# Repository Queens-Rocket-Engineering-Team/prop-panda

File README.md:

# PANDA Control Board

PANDA (Propulsion Actuation and Nominal Data Acquisition) is the control PCB for the Queen's Rocket Engineering Team's
hybrid rocket engine. During launch, PANDA controls systems on the fill plumbing panel, controls rocket ignition, and
provides pre-launch data acquisition. PANDA also functions as a standalone static fire test stand controller that
can execute all aspects of a hot-fire test.

## Assembled PCB

## System Architecture

PANDA uses an ESP32S3-WROOM-1U microcontroller for systems control. This ESP32S3 communicates with an external control
server to for remote control and data streaming over 2.4GHz WiFi. All commands are sent from the external server, as
PANDA does not autonomously control any systems.

Five ADS112C04 ADCs provide sensor readings to the ESP32S3 over an I2C bus. Sensors supported are:

- 6 pressure transducers
- 4 thermocouples
- 2 load cells

PANDA is also capable of monitoring ignitor characteristics. Measurements of the current passing through a nichrome wire
ignitor are obtained using a current sense amplifier across a shunt resistor in the ignitor path. Ignitor resistance
readings are also measured by injecting a small current from an IDAC on an ADC, and
measuring the resulting voltage.

A communications diagram for PANDA can be seen below.

```mermaid
---
title: PANDA Communications Flow
---
flowchart LR

    ADC(ADS112C04<br>ADCs) <==I2C==> ESP(ESP32 MCU)

    subgraph Controls
        AV(Actuated Valves)
        24VSAFE[24VSAFE<br>Relay]
        RUN[Ignitor Run<br>Relay]
        PRIME[Ignitor Prime<br>Relay]
    end

    subgraph Sensors
        PT(Pressure Transducers)
        TC(Thermocouples)
        LC(Load Cells)
        CUR(Ignitor Current)
        RES(Ignitor Resistance)
    end

    PT --> ADC
    TC --> ADC
    LC --> ADC
    CUR --> ADC
    RES --> ADC

    ESP --> AV
    ESP -->24VSAFE
    ESP --> RUN
    ESP --> PRIME

    ESP <-. WiFI .-> WIFI(External Server)
```

## Power Architecture

PANDA operates from a 24VDC power supply, and has a maximum current rating of 10A. The 24V rail is first stepped down to 5.3V with a switching converter and then dropped to 5V and 3.3V with LDOs. The 5V rail supplies analog systems, and the 3.3V rail supplies digital systems. Using LDOs on the switching output allows for low-noise power for analog measurements.

The 24VSAFE rail is only be energized when the fill panel is vacated, as it powers hazardous components such as the ignitor. The ignitor utilizes two relays in series for additional redundancy, and to ensure ignition is always intentional. A power distribution chart of PANDA can be seen below. This graph does not include the power sequencing and filtering present on the board.

```mermaid
---
title: PANDA Power Distribution
---
flowchart LR

    24VIN([24VIN]) --> 24VSAFE[24VSAFE<br>Relay]

    subgraph Valves
        AV(Valves)
        AVSAFE(Fill Valve<br>Run Valve)
    end
    24VIN --> AV
    24VSAFE --> AVSAFE

    subgraph Ignitor
        RUN[Ignitor Run<br>Relay]
        RUN --> PRIME[Ignitor Prime<br>Relay]
        PRIME --> IGN(Ignitor)
    end

    24VSAFE --> RUN[Ignitor Run<br>Relay]

    subgraph Voltage Regulation
        BUCK([5.3V Buck])
        BUCK --> 5V([5V LDO])
        BUCK --> 3V3([3.3V LDO])
    end

    24VIN --> BUCK([5.3V Buck])

    subgraph Sensors
        PT(Pressure Transducers)
        LC(Load Cells)
        RES(Ignitor Current<br>Sensor)
    end

    5V --> ADC(ADS112C04<br>ADCs)
    3V3 --> ESP(ESP32 MCU)
    3V3 --> ADC
    24VIN --> PT
    5V --> LC
    5V --> RES
```

## Required Software

This project was created using KiCad v9.0. If manufacturing with JLCPCB, install the Fabrication Toolkit KiCad plugin for JLCPCB.

## Recommended Manufacturing Options

If ordering from JLCPCB, use the JLC04161H-3313 stackup option. For JLC PCBA, the standard PCBA option is required due
to the ESP32S3-WROOM-1U being unavailable as a part in the economic PCBA assembly.

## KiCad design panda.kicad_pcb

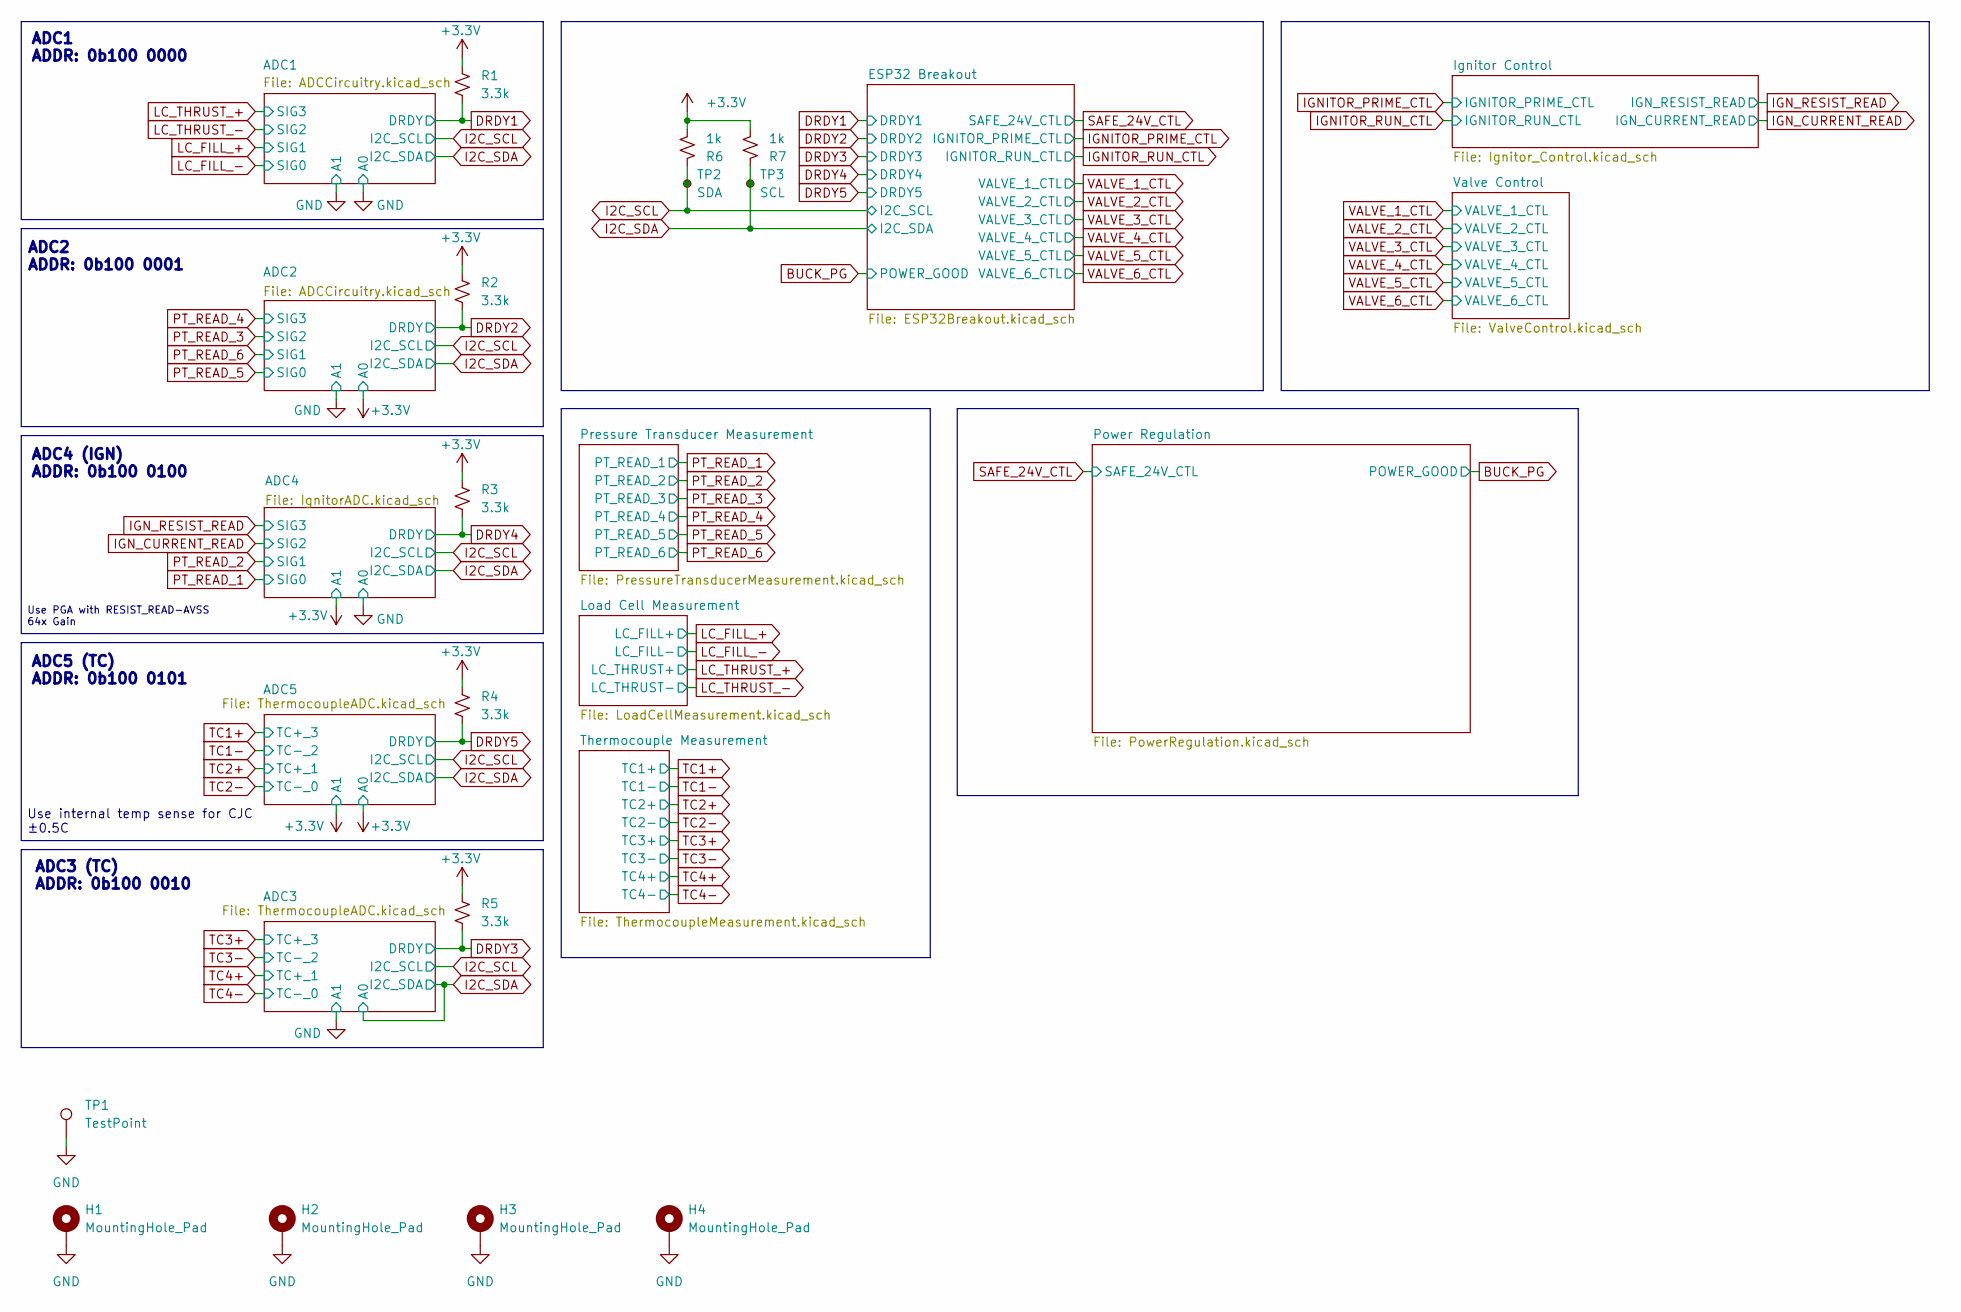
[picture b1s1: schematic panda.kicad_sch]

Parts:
H1, H2, H3, H4: MountingHole_Pad; MountingHole_3.2mm_M3_ISO7380_Pad
R1, R2, R3, R4, R5: 3.3k; R_0402_1005Metric; MPN 0402WGF3301TCE; LCSC C25890
R6, R7: 1k; R_0402_1005Metric; LCSC C11702
TP1: TestPoint; TestPoint_Loop_D2.50mm_Drill1.0mm
TP2: SDA; TestPoint_Pad_D1.5mm
TP3: SCL; TestPoint_Pad_D1.5mm

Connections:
DRDY1: R1.2; also elsewhere on the board
DRDY2: R2.2; also elsewhere on the board
DRDY3: R5.2; also elsewhere on the board
DRDY4: R3.2; also elsewhere on the board
DRDY5: R4.2; also elsewhere on the board
I2C_SCL: R6.1, TP2.1; also elsewhere on the board
I2C_SDA: R7.1, TP3.1; also elsewhere on the board

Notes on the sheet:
ADC2 ADDR: 0b100 0001
ADC4 (IGN) ADDR: 0b100 0100
Use PGA with RESIST_READ-AVSS 64x Gain
ADC1 ADDR: 0b100 0000
ADC3 (TC) ADDR: 0b100 0010
Use internal temp sense for CJC ±0.5C
ADC5 (TC) ADDR: 0b100 0101

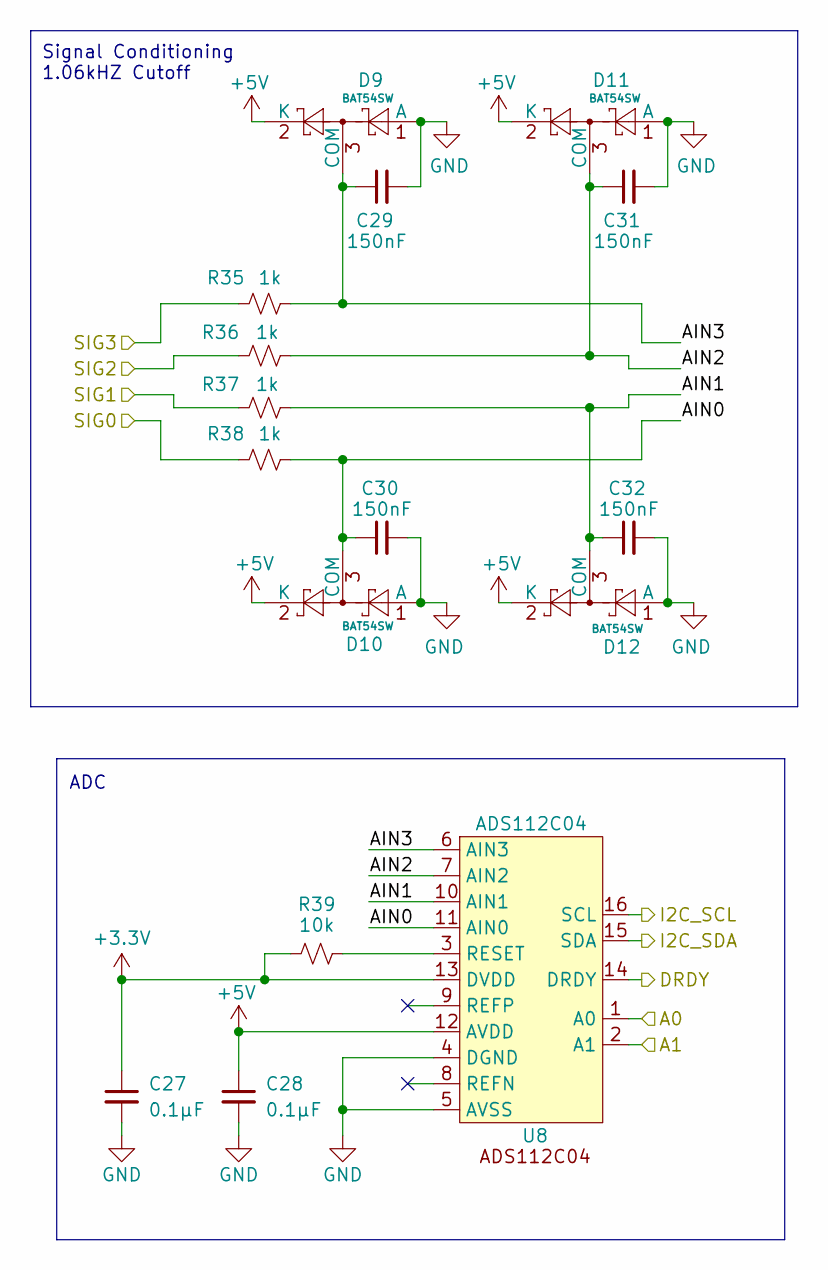
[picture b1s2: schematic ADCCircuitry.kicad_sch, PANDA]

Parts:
C27, C28: 0.1μF; C_0402_1005Metric; MPN CL05B104KO5NNNC; LCSC C307331
C29, C30, C31, C32: 150nF; C_0402_1005Metric; LCSC C576725
D9, D10, D11, D12: BAT54SW; SOT-323_SC-70; LCSC C83575
R35, R36, R37, R38: 1k; R_0402_1005Metric
R39: 10k; R_0402_1005Metric; MPN 0402WGJ0103TCE; LCSC C25531
U8: ADS112C04; TSSOP-16_4.4x5mm_P0.65mm; MPN ADS112C04IPWR; LCSC C701615

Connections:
+5V: C28.1, D9.2 (K), D10.2 (K), D11.2 (K), D12.2 (K), U8.12 (AVDD); also elsewhere on the board
/ADC1/AIN0: C30.1, D10.3 (COM), R38.2, U8.11 (AIN0)
/ADC1/AIN1: C32.1, D12.3 (COM), R37.2, U8.10 (AIN1)
/ADC1/AIN2: C31.1, D11.3 (COM), R36.2, U8.7 (AIN2)
/ADC1/AIN3: C29.1, D9.3 (COM), R35.2, U8.6 (AIN3)
DRDY1: U8.14 (DRDY); also elsewhere on the board
I2C_SCL: U8.16 (SCL); also elsewhere on the board
I2C_SDA: U8.15 (SDA); also elsewhere on the board
LC_FILL_+: R37.1; also elsewhere on the board
LC_FILL_-: R38.1; also elsewhere on the board
LC_THRUST_+: R35.1; also elsewhere on the board
LC_THRUST_-: R36.1; also elsewhere on the board
unnamed: R39.2, U8.3 (RESET)

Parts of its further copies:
C33, C34: 0.1μF; C_0402_1005Metric; MPN CL05B104KO5NNNC; LCSC C307331
C35, C36, C37, C38: 150nF; C_0402_1005Metric; LCSC C576725
D13, D14, D15, D16: BAT54SW; SOT-323_SC-70; LCSC C83575
R40, R41, R42, R43: 1k; R_0402_1005Metric
R44: 10k; R_0402_1005Metric; MPN 0402WGJ0103TCE; LCSC C25531
U9: ADS112C04; TSSOP-16_4.4x5mm_P0.65mm; MPN ADS112C04IPWR; LCSC C701615

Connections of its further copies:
+5V: C34.1, D13.2 (K), D14.2 (K), D15.2 (K), D16.2 (K), U9.12 (AVDD); also elsewhere on the board
/ADC2/AIN0: C36.1, D14.3 (COM), R43.2, U9.11 (AIN0)
/ADC2/AIN1: C38.1, D16.3 (COM), R42.2, U9.10 (AIN1)
/ADC2/AIN2: C37.1, D15.3 (COM), R41.2, U9.7 (AIN2)
/ADC2/AIN3: C35.1, D13.3 (COM), R40.2, U9.6 (AIN3)
DRDY2: U9.14 (DRDY); also elsewhere on the board
I2C_SCL: U9.16 (SCL); also elsewhere on the board
I2C_SDA: U9.15 (SDA); also elsewhere on the board
unnamed: R44.2, U9.3 (RESET)
PT_READ_3: R41.1; also elsewhere on the board
PT_READ_4: R40.1; also elsewhere on the board
PT_READ_5: R43.1; also elsewhere on the board
PT_READ_6: R42.1; also elsewhere on the board

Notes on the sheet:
ADC
Signal Conditioning 1.06kHZ Cutoff

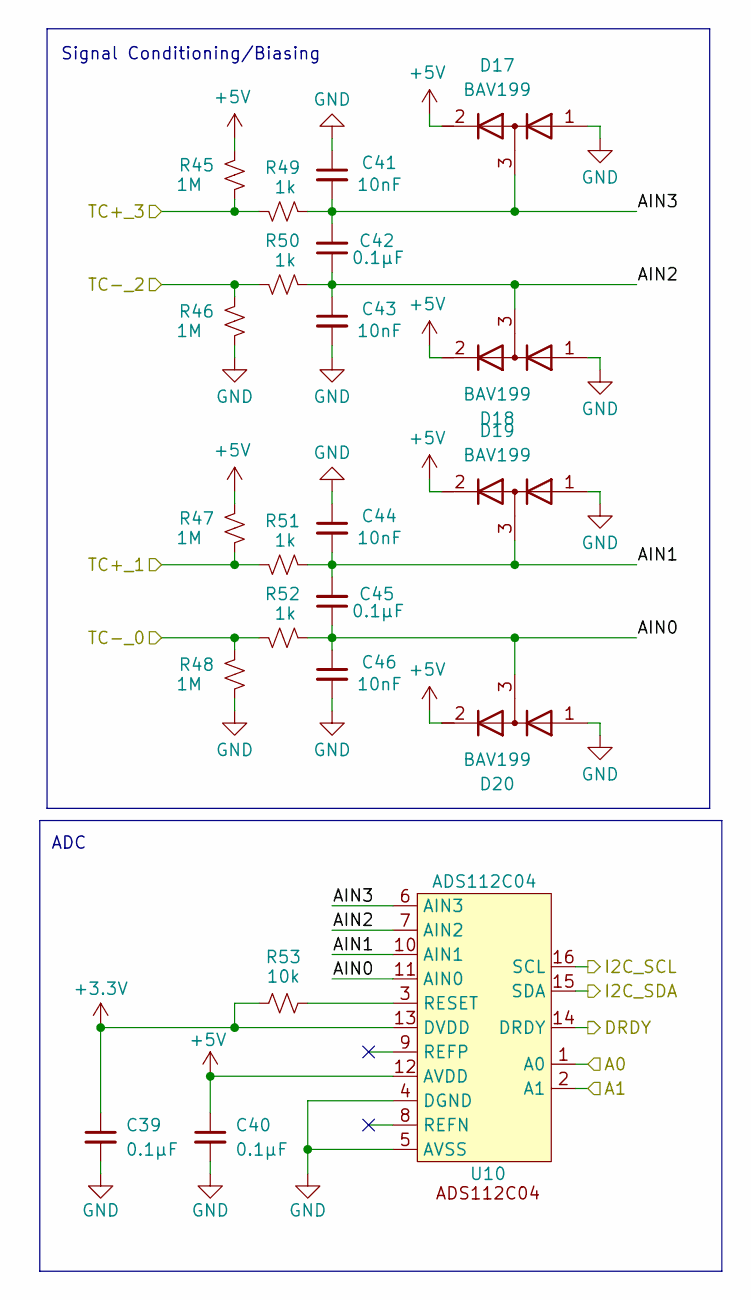
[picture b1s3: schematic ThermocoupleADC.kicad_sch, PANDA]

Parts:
C39, C40, C42, C45: 0.1μF; C_0402_1005Metric; MPN CL05B104KO5NNNC; LCSC C307331
C41, C43, C44, C46: 10nF; C_0603_1608Metric; LCSC C5299898
D17, D18, D19, D20: BAV199; SOT-23; LCSC C40919
R45, R46, R47, R48: 1M; R_0402_1005Metric
R49, R50, R51, R52: 1k; R_0402_1005Metric
R53: 10k; R_0402_1005Metric; MPN 0402WGJ0103TCE; LCSC C25531
U10: ADS112C04; TSSOP-16_4.4x5mm_P0.65mm; MPN ADS112C04IPWR; LCSC C701615

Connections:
+5V: C40.1, D17.2 (K), D18.2 (K), D19.2 (K), D20.2 (K), R45.2, R47.2, U10.12 (AVDD); also elsewhere on the board
/ADC5/AIN0: C45.1, C46.1, D20.3 (common), R52.2, U10.11 (AIN0)
/ADC5/AIN1: C44.2, C45.2, D19.3 (common), R51.2, U10.10 (AIN1)
/ADC5/AIN2: C42.1, C43.1, D18.3 (common), R50.2, U10.7 (AIN2)
/ADC5/AIN3: C41.2, C42.2, D17.3 (common), R49.2, U10.6 (AIN3)
DRDY5: U10.14 (DRDY); also elsewhere on the board
I2C_SCL: U10.16 (SCL); also elsewhere on the board
I2C_SDA: U10.15 (SDA); also elsewhere on the board
unnamed: R53.2, U10.3 (RESET)
TC1+: R45.1, R49.1; also elsewhere on the board
TC1-: R46.2, R50.1; also elsewhere on the board
TC2+: R47.1, R51.1; also elsewhere on the board
TC2-: R48.2, R52.1; also elsewhere on the board

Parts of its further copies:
C47, C48, C50, C53: 0.1μF; C_0402_1005Metric; MPN CL05B104KO5NNNC; LCSC C307331
C49, C51, C52, C54: 10nF; C_0603_1608Metric; LCSC C5299898
D21, D22, D23, D24: BAV199; SOT-23; LCSC C40919
R54, R55, R56, R57: 1M; R_0402_1005Metric
R58, R59, R60, R61: 1k; R_0402_1005Metric
R62: 10k; R_0402_1005Metric; MPN 0402WGJ0103TCE; LCSC C25531
U11: ADS112C04; TSSOP-16_4.4x5mm_P0.65mm; MPN ADS112C04IPWR; LCSC C701615

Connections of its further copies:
+5V: C48.1, D21.2 (K), D22.2 (K), D23.2 (K), D24.2 (K), R54.2, R56.2, U11.12 (AVDD); also elsewhere on the board
/ADC3/AIN0: C53.1, C54.1, D24.3 (common), R61.2, U11.11 (AIN0)
/ADC3/AIN1: C52.2, C53.2, D23.3 (common), R60.2, U11.10 (AIN1)
/ADC3/AIN2: C50.1, C51.1, D22.3 (common), R59.2, U11.7 (AIN2)
/ADC3/AIN3: C49.2, C50.2, D21.3 (common), R58.2, U11.6 (AIN3)
DRDY3: U11.14 (DRDY); also elsewhere on the board
I2C_SCL: U11.16 (SCL); also elsewhere on the board
I2C_SDA: U11.1 (A0), U11.15 (SDA); also elsewhere on the board
unnamed: R62.2, U11.3 (RESET)
TC3+: R54.1, R58.1; also elsewhere on the board
TC3-: R55.2, R59.1; also elsewhere on the board
TC4+: R56.1, R60.1; also elsewhere on the board
TC4-: R57.2, R61.1; also elsewhere on the board

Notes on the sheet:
ADC
Signal Conditioning/Biasing

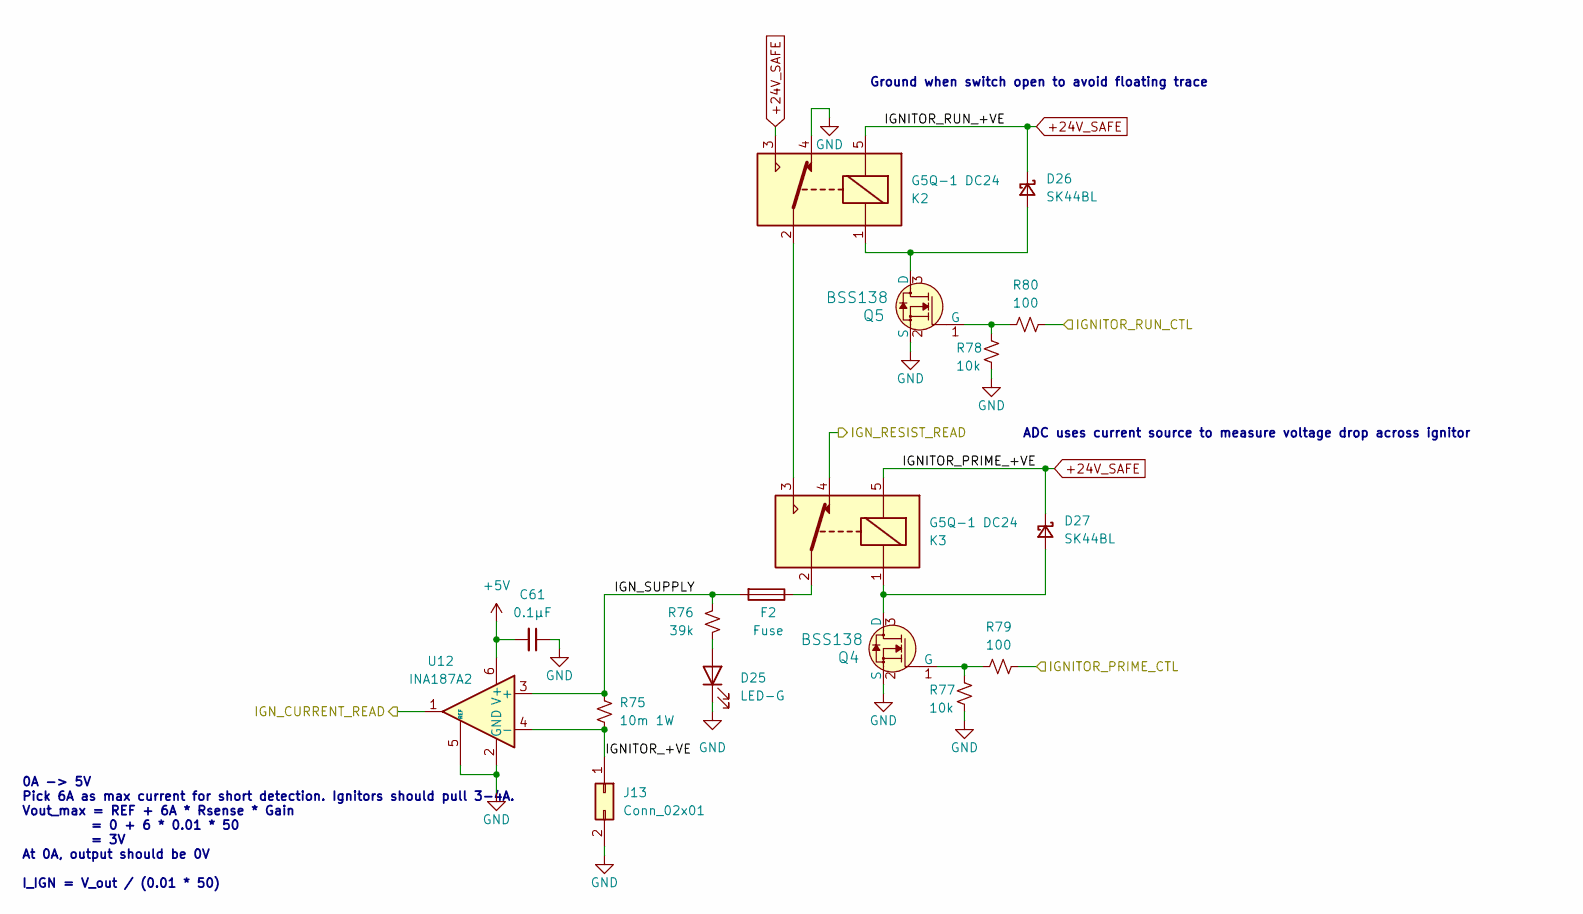
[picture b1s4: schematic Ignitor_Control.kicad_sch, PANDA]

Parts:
C61: 0.1μF; C_0402_1005Metric; MPN CL05B104KO5NNNC; LCSC C307331
D25: LED-G; LED_0805_2012Metric; LCSC C2297
D26, D27: SK44BL; D_SMB; MPN SK44BL-TP; LCSC C151740
F2: Fuse; Fuseholder_Blade_Mini_Keystone_3568
J13: Conn_02x01; Molex_Mini-Fit_Jr_5566-02A_2x01_P4.20mm_Vertical
K2, K3: G5Q-1 DC24; Relay_SPDT_Omron-G5Q-1
Q4, Q5: BSS138; SOT-23-3; MPN BSS138; LCSC C8490
R75: 10m 1W; R_1206_3216Metric
R76: 39k; R_0402_1005Metric
R77, R78: 10k; R_0402_1005Metric; MPN 0402WGJ0103TCE; LCSC C25531
R79, R80: 100; R_0402_1005Metric; MPN 0402WGF1000TCE; LCSC C25076
U12: INA187A2; SOT-23-6; LCSC C49262295

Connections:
+5V: C61.2, U12.6 (V+); also elsewhere on the board
+24V_SAFE: D26.1 (K), D27.1 (K), K2.3, K2.5, K3.5; also elsewhere on the board
/Ignitor Control/IGNITOR_+VE: J13.1, R75.2, U12.4 (-)
/Ignitor Control/IGN_SUPPLY: F2.2, R75.1, R76.2, U12.3 (+)
IGNITOR_PRIME_CTL: R79.2; also elsewhere on the board
IGNITOR_RUN_CTL: R80.2; also elsewhere on the board
IGN_CURRENT_READ: U12.1; also elsewhere on the board
IGN_RESIST_READ: K3.4; also elsewhere on the board
unnamed: D25.2 (A), R76.1
unnamed: D26.2 (A), K2.1, Q5.3 (D)
unnamed: D27.2 (A), K3.1, Q4.3 (D)
unnamed: F2.1, K3.2
unnamed: K2.2, K3.3
unnamed: Q4.1 (G), R77.1, R79.1
unnamed: Q5.1 (G), R78.1, R80.1

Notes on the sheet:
0A -> 5V Pick 6A as max current for short detection. Ignitors should pull 3-4A. Vout_max = REF + 6A * Rsense * Gain = 0 + 6 * 0.01 * 50 = 3V At 0A, output should be 0V I_IGN = V_out / (0.01 * 50)
Ground when switch open to avoid floating trace
ADC uses current source to measure voltage drop across ignitor

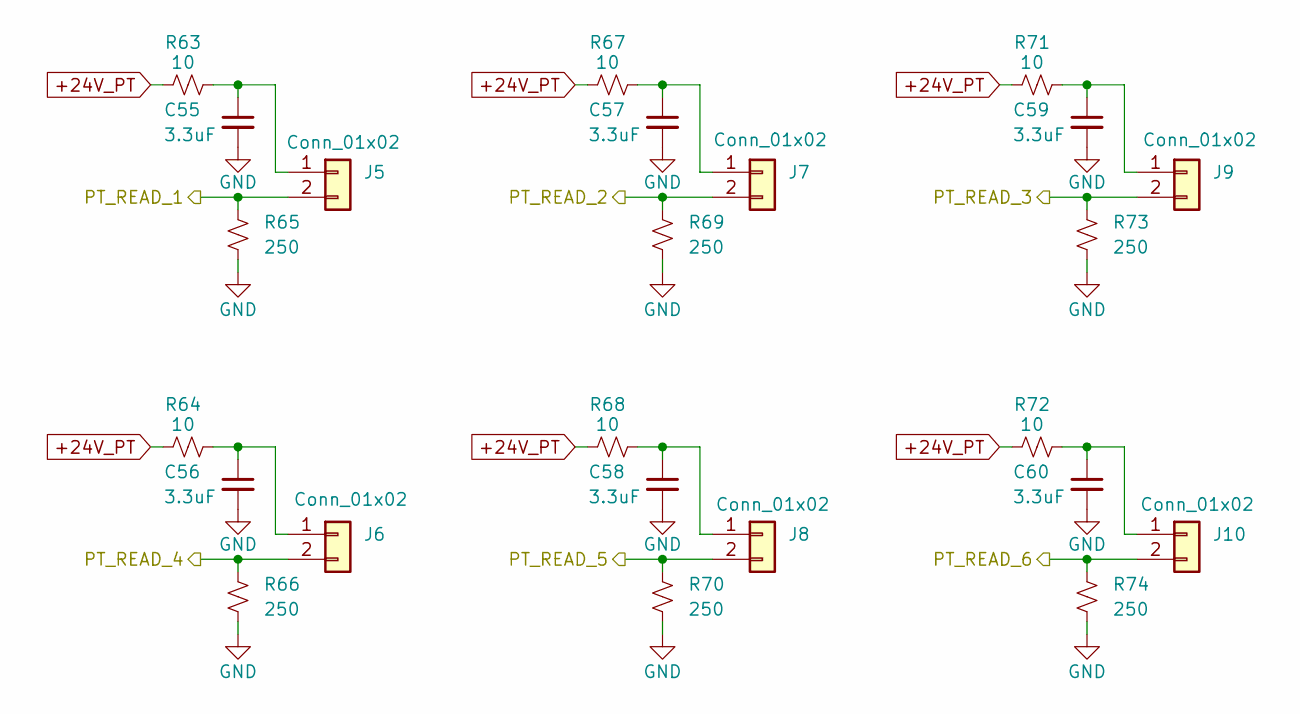
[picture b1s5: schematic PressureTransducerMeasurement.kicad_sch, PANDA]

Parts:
C55, C56, C57, C58, C59, C60: 3.3uF; C_0805_2012Metric; LCSC C342775
J5, J6, J7, J8, J9, J10: Conn_01x02; Molex_Micro-Fit_3.0_43650-0215_1x02_P3.00mm_Vertical
R63, R64, R67, R68, R71, R72: 10; R_0402_1005Metric
R65, R66, R69, R70, R73, R74: 250; R_0603_1608Metric; MPN RT0603BRE07250RL; LCSC C861779

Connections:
+24V_PT: R63.1, R64.1, R67.1, R68.1, R71.1, R72.1; also elsewhere on the board
unnamed: C55.1, J5.1, R63.2
unnamed: C56.1, J6.1, R64.2
unnamed: C57.1, J7.1, R67.2
unnamed: C58.1, J8.1, R68.2
unnamed: C59.1, J9.1, R71.2
unnamed: C60.1, J10.1, R72.2
PT_READ_1: J5.2, R65.1; also elsewhere on the board
PT_READ_2: J7.2, R69.1; also elsewhere on the board
PT_READ_3: J9.2, R73.1; also elsewhere on the board
PT_READ_4: J6.2, R66.1; also elsewhere on the board
PT_READ_5: J8.2, R70.1; also elsewhere on the board
PT_READ_6: J10.2, R74.1; also elsewhere on the board

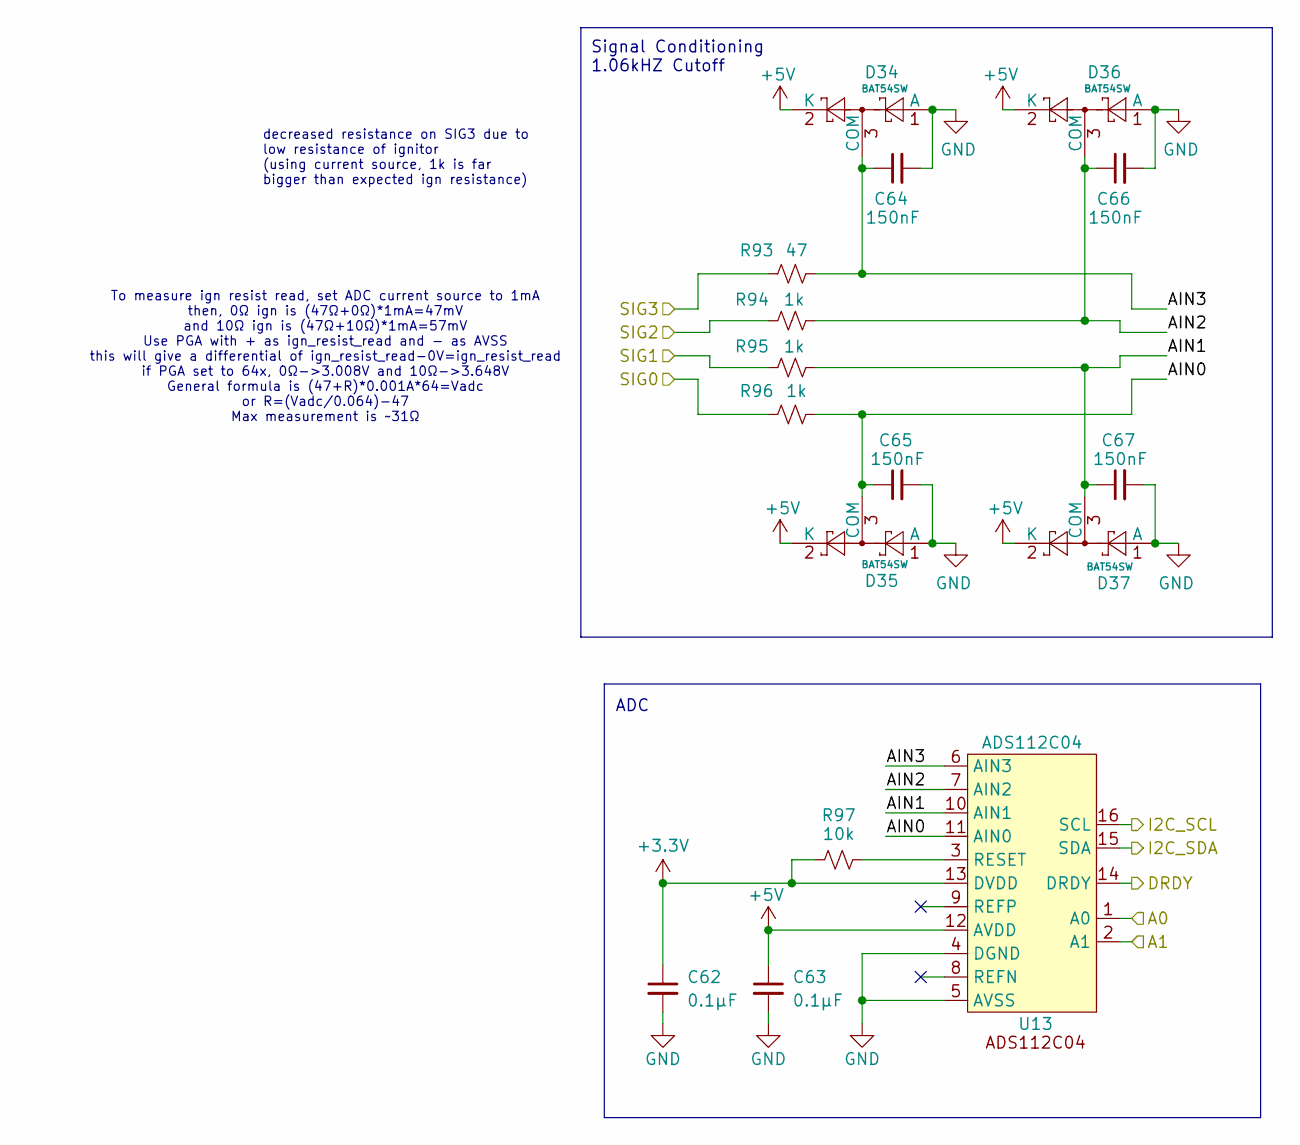
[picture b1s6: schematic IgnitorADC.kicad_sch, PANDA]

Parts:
C62, C63: 0.1μF; C_0402_1005Metric; MPN CL05B104KO5NNNC; LCSC C307331
C64, C65, C66, C67: 150nF; C_0402_1005Metric; LCSC C576725
D34, D35, D36, D37: BAT54SW; SOT-323_SC-70; LCSC C83575
R93: 47; R_0402_1005Metric; LCSC C445569
R94, R95, R96: 1k; R_0402_1005Metric
R97: 10k; R_0402_1005Metric; MPN 0402WGJ0103TCE; LCSC C25531
U13: ADS112C04; TSSOP-16_4.4x5mm_P0.65mm; MPN ADS112C04IPWR; LCSC C701615

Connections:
+5V: C63.1, D34.2 (K), D35.2 (K), D36.2 (K), D37.2 (K), U13.12 (AVDD); also elsewhere on the board
/ADC4/AIN0: C65.1, D35.3 (COM), R96.2, U13.11 (AIN0)
/ADC4/AIN1: C67.1, D37.3 (COM), R95.2, U13.10 (AIN1)
/ADC4/AIN2: C66.1, D36.3 (COM), R94.2, U13.7 (AIN2)
/ADC4/AIN3: C64.1, D34.3 (COM), R93.2, U13.6 (AIN3)
DRDY4: U13.14 (DRDY); also elsewhere on the board
I2C_SCL: U13.16 (SCL); also elsewhere on the board
I2C_SDA: U13.15 (SDA); also elsewhere on the board
IGN_CURRENT_READ: R94.1; also elsewhere on the board
IGN_RESIST_READ: R93.1; also elsewhere on the board
unnamed: R97.2, U13.3 (RESET)
PT_READ_1: R96.1; also elsewhere on the board
PT_READ_2: R95.1; also elsewhere on the board

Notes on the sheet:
To measure ign resist read, set ADC current source to 1mA then, 0Ω ign is (47Ω+0Ω)*1mA=47mV and 10Ω ign is (47Ω+10Ω)*1mA=57mV Use PGA with + as ign_resist_read and - as AVSS this will give a differential of ign_resist_read-0V=ign_resist_read if PGA set to 64x, 0Ω->3.008V and 10Ω->3.648V General for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
ADC
decreased resistance on SIG3 due to low resistance of ignitor (using current source, 1k is far bigger than expected ign resistance)
Signal Conditioning 1.06kHZ Cutoff

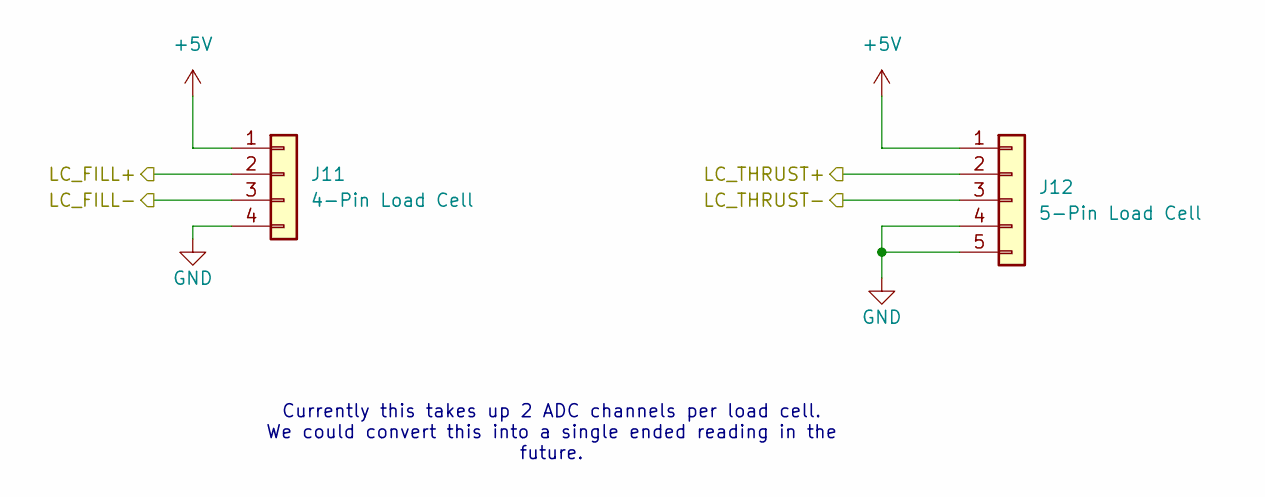
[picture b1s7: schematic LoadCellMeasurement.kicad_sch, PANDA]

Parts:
J11: 4-Pin Load Cell; Molex_Micro-Fit_3.0_43650-0415_1x04_P3.00mm_Vertical
J12: 5-Pin Load Cell; Molex_Micro-Fit_3.0_43650-0515_1x05_P3.00mm_Vertical

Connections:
+5V: J11.1, J12.1; also elsewhere on the board
LC_FILL_+: J11.2; also elsewhere on the board
LC_FILL_-: J11.3; also elsewhere on the board
LC_THRUST_+: J12.2; also elsewhere on the board
LC_THRUST_-: J12.3; also elsewhere on the board

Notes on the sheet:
Currently this takes up 2 ADC channels per load cell. We could convert this into a single ended reading in the future.

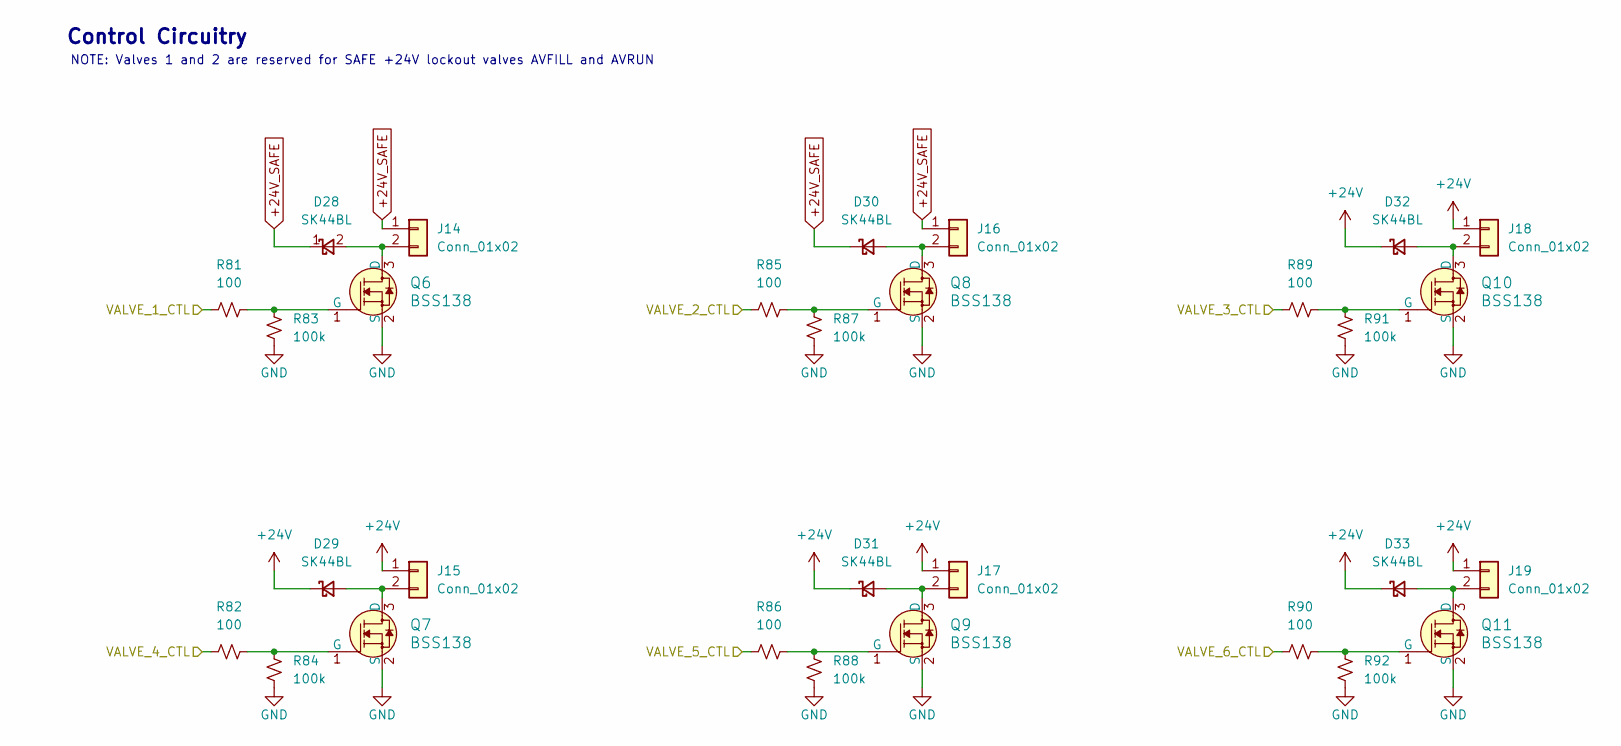
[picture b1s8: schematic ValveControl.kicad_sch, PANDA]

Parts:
D28, D29, D30, D31, D32, D33: SK44BL; D_SMB; MPN SK44BL-TP; LCSC C151740
J14, J15, J16, J17, J18, J19: Conn_01x02; Molex_Micro-Fit_3.0_43650-0215_1x02_P3.00mm_Vertical
Q6, Q7, Q8, Q9: BSS138; SOT-23-3; MPN BSS138; LCSC C8490
Q10, Q11: BSS138; SOT-23-3; MPN BSS138; Digi-Key_PN BSS138CT-ND
R81, R82, R85, R86, R89, R90: 100; R_0402_1005Metric; MPN 0402WGF1000TCE; LCSC C25076
R83, R84, R87, R88, R91, R92: 100k; R_0603_1608Metric; MPN 0402WGJ0104TCE; LCSC C25530

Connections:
+24V: D29.1 (K), D31.1 (K), D32.1 (K), D33.1 (K), J15.1, J17.1, J18.1, J19.1; also elsewhere on the board
+24V_SAFE: D28.1 (K), D30.1 (K), J14.1, J16.1; also elsewhere on the board
unnamed: D28.2 (A), J14.2, Q6.3 (D)
unnamed: D29.2 (A), J15.2, Q7.3 (D)
unnamed: D30.2 (A), J16.2, Q8.3 (D)
unnamed: D31.2 (A), J17.2, Q9.3 (D)
unnamed: D32.2 (A), J18.2, Q10.3 (D)
unnamed: D33.2 (A), J19.2, Q11.3 (D)
unnamed: Q6.1 (G), R81.2, R83.1
unnamed: Q7.1 (G), R82.2, R84.1
unnamed: Q8.1 (G), R85.2, R87.1
unnamed: Q9.1 (G), R86.2, R88.1
unnamed: Q10.1 (G), R89.2, R91.1
unnamed: Q11.1 (G), R90.2, R92.1
VALVE_1_CTL: R81.1; also elsewhere on the board
VALVE_2_CTL: R85.1; also elsewhere on the board
VALVE_3_CTL: R89.1; also elsewhere on the board
VALVE_4_CTL: R82.1; also elsewhere on the board
VALVE_5_CTL: R86.1; also elsewhere on the board
VALVE_6_CTL: R90.1; also elsewhere on the board

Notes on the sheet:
NOTE: Valves 1 and 2 are reserved for SAFE +24V lockout valves AVFILL and AVRUN
Control Circuitry

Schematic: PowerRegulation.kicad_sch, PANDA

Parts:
BZ1: YS-SBZ9650DYB05; LCSC C409830
C1, C7, C14, C15, C18, C19, C21: 0.1μF; C_0402_1005Metric; MPN CL05B104KO5NNNC; LCSC C307331
C2: 100uF; CP_Elec_10x10; LCSC C161937
C3: 10uF; C_1812_4532Metric; Voltage 50V
C4: 10uF; C_1206_3216Metric; Voltage 50V; LCSC C13585
C5: 220nF; C_0805_2012Metric; Voltage 50V; LCSC C5378
C6: 1uF; C_0603_1608Metric; LCSC C29936
C8, C13, C17, C20: 10uF; C_0805_2012Metric; LCSC C15850
C9: 3pF; C_0603_1608Metric; LCSC C695157
C10, C12: 22uF; C_0805_2012Metric; LCSC C602037
C11: 10nF; C_0402_1005Metric; LCSC C15195
C16: 2.2uF; C_0603_1608Metric; LCSC C23630
D1, D3, D4, D6, D7: LED-G; LED_0805_2012Metric; LCSC C2297
D2: SMCJ26A-13-F; D_SMC; LCSC C135156
D5, D38: SK44BL; D_SMB; MPN SK44BL-TP; LCSC C151740
F1: Fuse; Fuseholder_Blade_Mini_Keystone_3568
J1: Conn_01x02; Molex_Micro-Fit_3.0_43650-0215_1x02_P3.00mm_Vertical
J2, J3: Conn_02x01; Molex_Mini-Fit_Jr_5566-02A_2x01_P4.20mm_Vertical
K1: G5Q-1A DC24; Relay_SPST_Omron-G5Q-1A
L1: 4.7uH; L_Bourns_SRP7028A_7.3x6.6mm; LCSC C840529
Q1, Q2, Q12: BSS138; SOT-23-3; MPN BSS138; LCSC C8490
Q3: DMP6023LE-13; SOT-223-3_TabPin2; LCSC C154901
R8, R10, R12, R14, R23: 100k; R_0603_1608Metric
R9, R11, R13: 39k; R_0402_1005Metric
R15: 10k; R_0402_1005Metric; MPN 0402WGJ0103TCE; LCSC C25531
R16: 100; R_0402_1005Metric; MPN 0402WGF1000TCE; LCSC C25076
R17: 470k; R_0603_1608Metric
R18, R19, R27, R98: 10k; R_0402_1005Metric
R20, R21: 100k; R_0603_1608Metric; MPN 0402WGJ0103TCE; LCSC C25531
R22: 23.2k; R_0603_1608Metric; MPN 0402WGF3301TCE; LCSC C25890
R24: 18k; R_0603_1608Metric
R25: 1.2k; R_0402_1005Metric
R26: 160k; R_0402_1005Metric
R28: 3.3k; R_0402_1005Metric
R99: 2.2k; R_0402_1005Metric
TP4: TP_+3.3V; TestPoint_Pad_D1.0mm
TP5: TP_+5V; TestPoint_Pad_D1.0mm
U1: LM3880-1AA; SOT-23-6; LCSC C486059
U2: LMR33630BDDA; Texas_HSOP-8-1EP_3.9x4.9mm_P1.27mm_ThermalVias; LCSC C544370
U3: TPS78533QKVURQ1; TO-252-4; LCSC C3748131
U4: TLC555xPS; VSSOP-8_3x3mm_P0.65mm
U5: TPS78450QDBVRQ1; SOT-23-5; LCSC C2877783
U6: LM66200DRLR; SOT-583-8; LCSC C3235556

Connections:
5V_USB: C19.2, U6.6 (VIN2); also elsewhere on the board
+5V: C20.1, R28.2, TP5.1, U5.5 (OUT); also elsewhere on the board
+24V: C2.1, C3.1, C4.1, C5.1, D2.1 (A1), D5.1 (K), F1.2, J3.2, K1.5, Q3.3 (S), R13.2, R18.2, U2.2 (VIN), U2.3 (EN); also elsewhere on the board
+24V_PT: Q3.2 (D); also elsewhere on the board
+24V_SAFE: K1.2, R11.2, R23.2, R98.2; also elsewhere on the board
/Power Regulation/+3.3V_EN: R10.1, U1.6 (FLAG1), U3.1 (EN)
/Power Regulation/+5.3V: BZ1.1 (+), C9.1, C10.1, C12.1, C14.2, C15.2, C18.2, D38.1 (K), L1.2, R21.1, R27.2, U4.8 (VCC), U6.3 (VIN1)
/Power Regulation/+5V_EN: R12.1, U1.5 (FLAG2), U5.3 (EN)
/Power Regulation/+24V_POST_LCKT: J3.1, K1.3, R9.2
/Power Regulation/PWR_SQ: C1.2, C8.1, C17.1, C21.2, J1.2, R10.2, R12.2, R14.2, U1.1 (VCC), U3.2 (IN), U5.1 (IN), U6.2 (VOUT), U6.7 (VOUT)
/Power Regulation/SW: C7.2, L1.1, U2.8 (SW)
/Power Regulation/TR: C16.1, R26.2, U4.2 (TR), U4.6 (THR)
/Power Regulation/VCC: C6.1, U2.6 (VCC)
BUCK_PG: R20.1, U2.4 (PG); also elsewhere on the board
unnamed: BZ1.2 (-), D38.2 (A), Q12.3 (D)
unnamed: D1.2 (A), R9.1
unnamed: D3.2 (A), R11.1
unnamed: D4.2 (A), R13.1
unnamed: D5.2 (A), K1.1, Q1.3 (D)
unnamed: D6.2 (A), R25.1
unnamed: D7.2 (A), R28.1
unnamed: J1.1, R8.2, U1.3 (EN)
unnamed: F1.1, J2.1
unnamed: Q1.1 (G), R15.1, R16.1
unnamed: Q2.3 (D), R19.1
unnamed: Q2.1 (G), R14.1, R17.2, U1.4 (FLAG3)
unnamed: Q3.1 (G), R18.1, R19.2
unnamed: Q12.1 (G), R98.1, R99.2
unnamed: Q12.2 (S), U4.3 (Q)
unnamed: C7.1, U2.7 (BOOT)
unnamed: C9.2, R21.2, R22.1, U2.5 (FB)
unnamed: C11.2, U4.5 (CV)
unnamed: R26.1, R27.1, U4.7 (DIS)
unnamed: R23.1, R24.2, U4.4 (R)
SAFE_24V_CTL: R16.2; also elsewhere on the board

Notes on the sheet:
USB ORing
Step-down Converter
Generates 2Hz square wave Buzzer frequency is 2.7KHz
FB R_{2} = (100k)/(V_{out} - 1)
+3.3V Regulation
+5V Regulation
Invert buzzer so 555 sinks current Buzzer pulls 30mA, TLC555 can sink 100mA TLC555 can only source 10mA
24V Input
+24V_SAFE Alert
Reset needs to be pulled higher than 1.8V to enable Set voltage divider to 3.66V
Power sequencing
Safe 24V

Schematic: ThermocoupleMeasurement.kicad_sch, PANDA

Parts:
J20: 395934308; CONN_SD-39543-002_NONE_08P_MOL

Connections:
TC1+: J20.2; also elsewhere on the board
TC1-: J20.1; also elsewhere on the board
TC2+: J20.4; also elsewhere on the board
TC2-: J20.3; also elsewhere on the board
TC3+: J20.6; also elsewhere on the board
TC3-: J20.5; also elsewhere on the board
TC4+: J20.8; also elsewhere on the board
TC4-: J20.7; also elsewhere on the board

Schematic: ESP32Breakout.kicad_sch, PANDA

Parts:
C22: 22uF; C_0805_2012Metric; LCSC C602037
C23, C25, C26: 0.1μF; C_0402_1005Metric; MPN CL05B104KO5NNNC; LCSC C307331
C24: 1uF; C_0603_1608Metric; LCSC C29936
CR1: USBLC6-2SC6; SOT-23-6; LCSC C7519
D8: LED-Y; LED_0805_2012Metric; LCSC C2296
J4: USB_C_Receptacle_USB2.0_16P; USB_C_Receptacle_G-Switch_GT-USB-7051x; LCSC C2843970
R29: 10k; R_0402_1005Metric
R30: 1k; R_0402_1005Metric
R31, R32: 5.1k; R_0402_1005Metric
R33: 270k; R_0402_1005Metric
R34: 39k; R_0402_1005Metric
SW1, SW2: USAKRO UK-B0227-G4.3-B-250; SW_Tactile_SPST_NO_Straight_CK_PTS636Sx25SMTRLFS; LCSC C556661
U7: ESP32-S3-WROOM-1U; LCSC C3013946

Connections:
5V_USB: C26.1, CR1.5, J4.A4 (VBUS), J4.A9 (VBUS), J4.B4 (VBUS), J4.B9 (VBUS); also elsewhere on the board
+24V_SAFE: R33.1; also elsewhere on the board
/ESP32 Breakout/24V_SAFE_DETECT: R33.2, R34.1, U7.7 (IO7)
/ESP32 Breakout/BOOT: SW2.1, U7.27 (IO0)
/ESP32 Breakout/D+: CR1.3, J4.A6 (D+), J4.B6 (D+)
/ESP32 Breakout/D-: CR1.1, J4.A7 (D-), J4.B7 (D-)
/ESP32 Breakout/RESET: C24.1, C25.1, R29.1, SW1.1, U7.3 (EN)
/ESP32 Breakout/USB_N: CR1.6, U7.13 (USB_D-)
/ESP32 Breakout/USB_P: CR1.4, U7.14 (USB_D+)
/ESP32 Breakout/WIFI_IND: R30.2, U7.39 (IO1)
BUCK_PG: U7.12 (IO8); also elsewhere on the board
DRDY1: U7.23 (IO21); also elsewhere on the board
DRDY2: U7.20 (IO12); also elsewhere on the board
DRDY3: U7.22 (IO14); also elsewhere on the board
DRDY4: U7.19 (IO11); also elsewhere on the board
DRDY5: U7.21 (IO13); also elsewhere on the board
I2C_SCL: U7.18 (IO10); also elsewhere on the board
I2C_SDA: U7.17 (IO9); also elsewhere on the board
IGNITOR_PRIME_CTL: U7.6 (IO6); also elsewhere on the board
IGNITOR_RUN_CTL: U7.5 (IO5); also elsewhere on the board
unnamed: D8.2 (A), R30.1
unnamed: J4.A5 (CC1), R31.1
unnamed: J4.B5 (CC2), R32.1
SAFE_24V_CTL: U7.4 (IO4); also elsewhere on the board
VALVE_1_CTL: U7.31 (IO38); also elsewhere on the board
VALVE_2_CTL: U7.32 (IO39); also elsewhere on the board
VALVE_3_CTL: U7.33 (IO40); also elsewhere on the board
VALVE_4_CTL: U7.34 (IO41); also elsewhere on the board
VALVE_5_CTL: U7.35 (IO42); also elsewhere on the board
VALVE_6_CTL: U7.38 (IO2); also elsewhere on the board

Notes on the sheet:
Wifi Indicator
24V_Safe detect
24V*(39/(39+270))=3.03V SAFE_DETECT

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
